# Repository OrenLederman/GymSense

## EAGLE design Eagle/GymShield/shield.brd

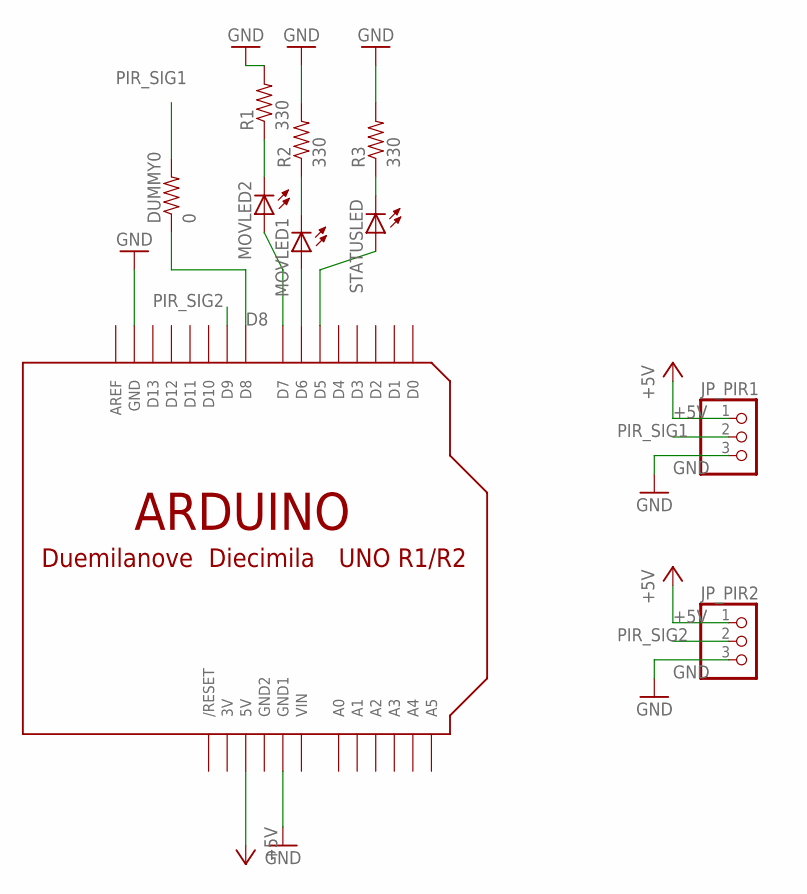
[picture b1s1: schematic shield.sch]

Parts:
DUMMY0: 0; AXIAL-0.4
JP_PIR1, JP_PIR2: PINHD-1X3; 1X03
MOVLED1, MOVLED2: LED5MM
R1, R2, R3: 330; AXIAL-0.4
STATUSLED: LED5MM
U$1: ARDUINOUNO; ARDUINO

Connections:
3V: U$1.3V
+5V: JP_PIR1.1, JP_PIR2.1, U$1.5V
D8: DUMMY0.P$1 (1), U$1.D8
GND: JP_PIR1.3, JP_PIR2.3, R1.P$2 (2), R2.P$2 (2), R3.P$2 (2), U$1.GND, U$1.GND1
GND2: U$1.GND2
unnamed: R3.P$1 (1), STATUSLED.K (C)
unnamed: MOVLED2.K (C), R1.P$1 (1)
unnamed: MOVLED1.K (C), R2.P$1 (1)
unnamed: STATUSLED.A, U$1.D5
unnamed: MOVLED1.A, U$1.D6
unnamed: MOVLED2.A, U$1.D7
PIR_SIG1: DUMMY0.P$2 (2), JP_PIR1.2
PIR_SIG2: JP_PIR2.2, U$1.D9
VIN: U$1.VIN

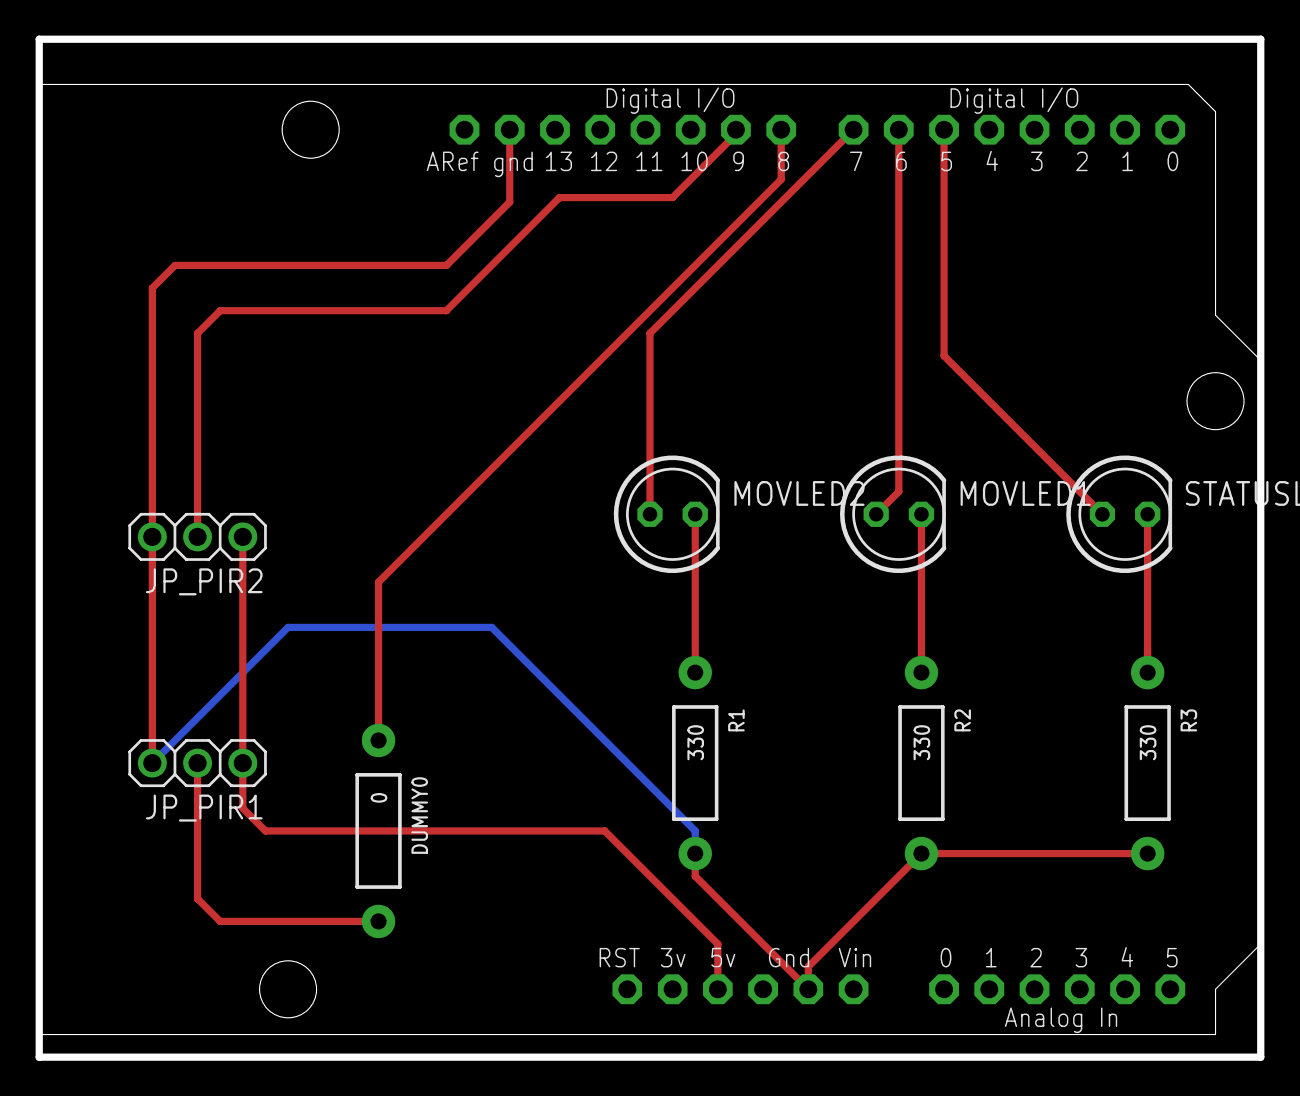
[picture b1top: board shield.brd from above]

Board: 2 copper layers, 68.6 x 57.1 mm, 10 parts (0 on the bottom side), 11 nets.

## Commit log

2015-01-25 First commit
    Eagle files
    Arduino code
2015-01-25 Adding NodeJS
2015-01-25 Removed .connect and .end
2015-01-25 Added Ethernet client code
    Just test code. Need to complete
2015-01-25 Added ActivityCount field
2015-01-25 Code for updating the database every 15 seconds
    Note - need to change the MAC and DHCP settings before deploying
2015-01-25 Updated MAC and DHCP settings
2015-01-25 dns fix, memory bug(?)
2015-01-25 added comment on Arduino version
2015-01-26 Added NodeJS code for showing the last time the equipment in the gym was used
2015-04-15 Added last activity scripts

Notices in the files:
parts and their libraries:
SparkFun-Resistors: Licensing: Creative Commons ShareAlike 4.0 International - https://creativecommons.org/licenses/by-sa/4.0
